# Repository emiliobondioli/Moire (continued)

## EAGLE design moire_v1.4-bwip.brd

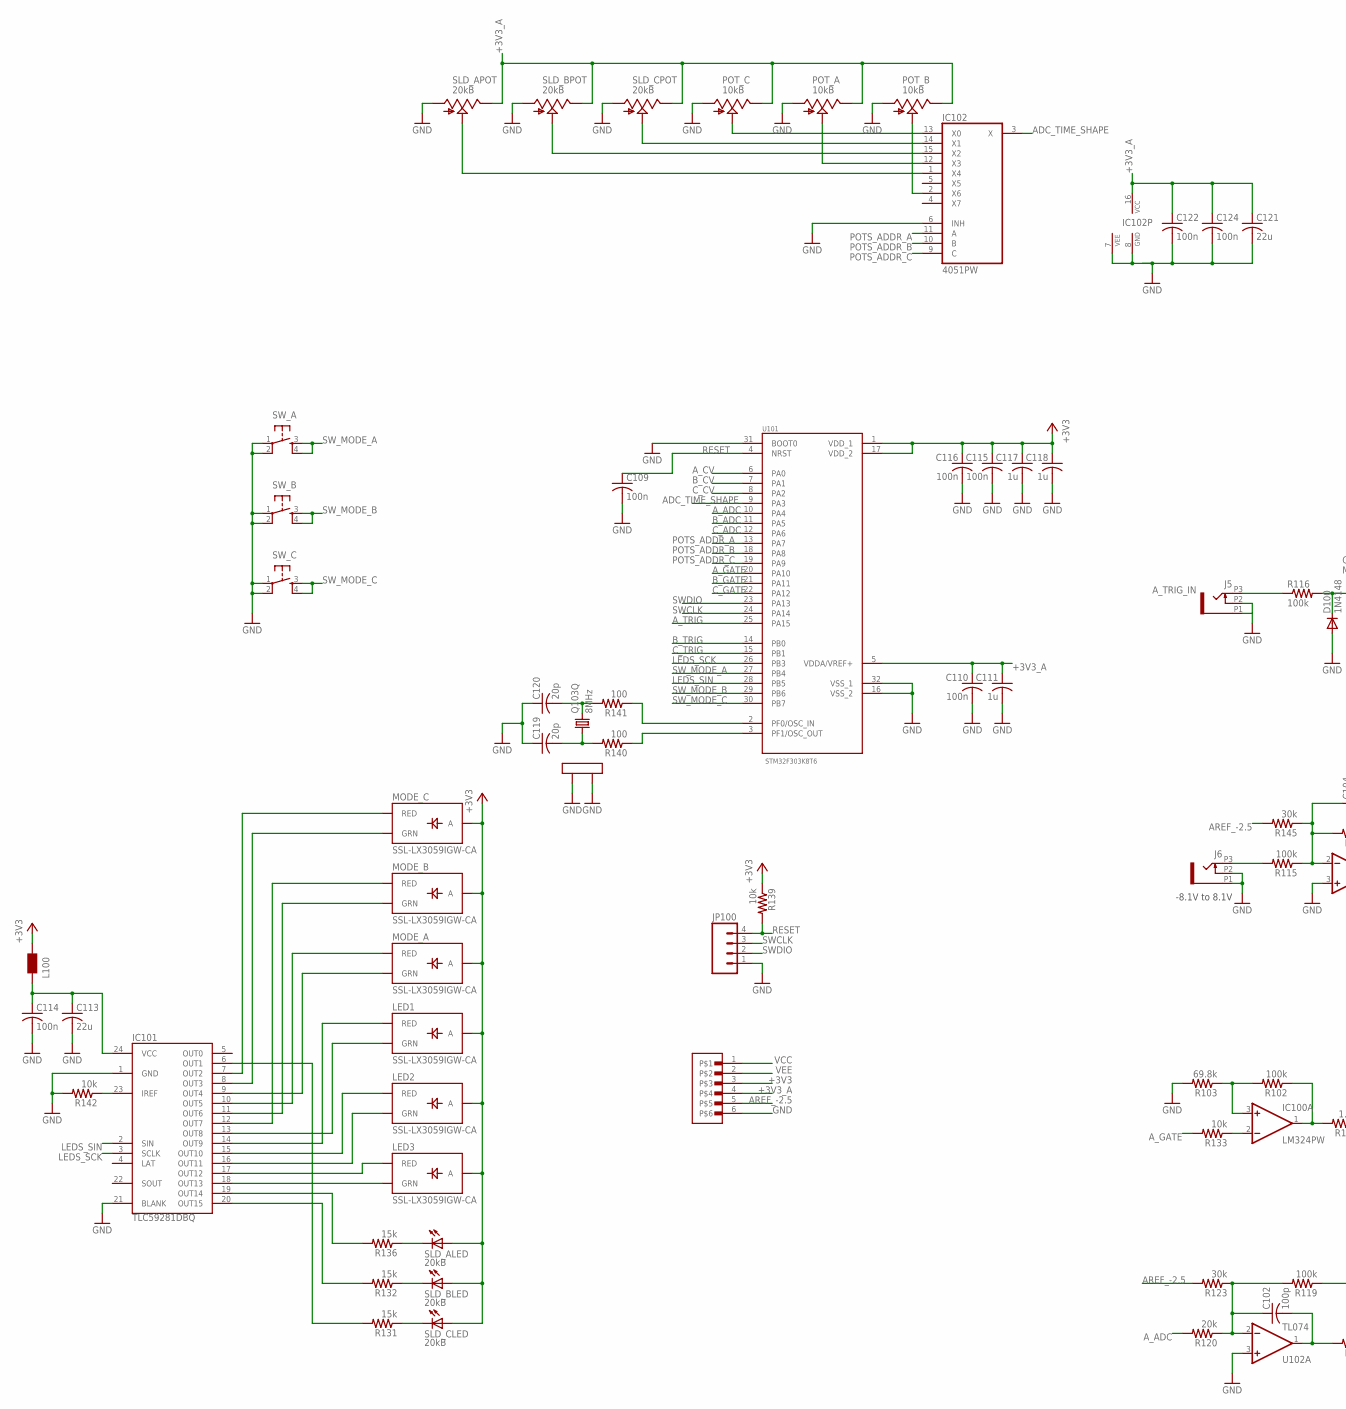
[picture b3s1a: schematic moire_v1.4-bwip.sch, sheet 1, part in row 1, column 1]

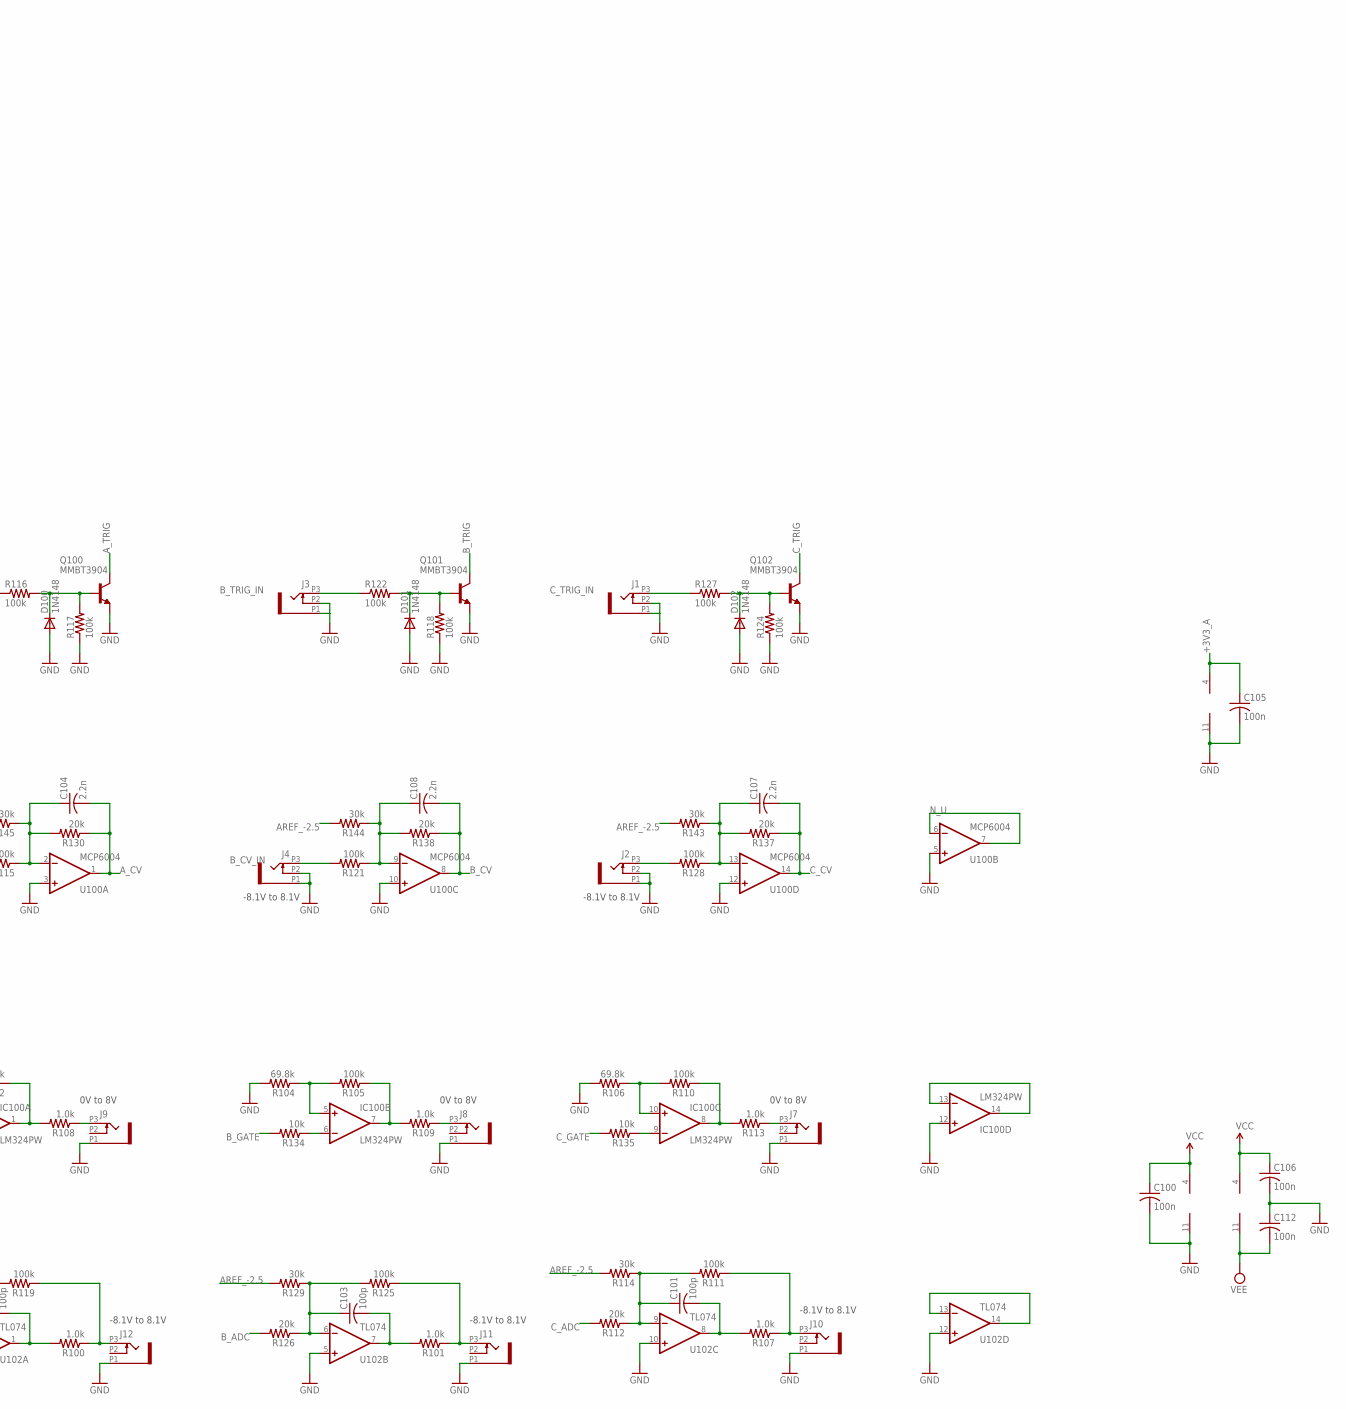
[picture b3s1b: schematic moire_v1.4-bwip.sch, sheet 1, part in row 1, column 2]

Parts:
C100, C105, C106, C109, C110, C112, C114, C115, C116, C122, C124: 100n; C0603
C101, C102, C103: 100p; C0603
C104, C107, C108: 2.2n; C0603
C111, C117, C118: 1u; C0603
C113, C121: 22u; C1206
C119, C120: 20p; C0603
D100, D101, D102: 1N4148; SOD523
IC100: LM324PW; TSSOP14_065
IC101: TLC59281DBQ; TSSOP24_0635
IC102: 4051PW; TSSOP16_065
J1, J2, J3, J4, J5, J6, J7, J8, J9, J10, J11, J12: PJ301_THONKICONN6; WQP_PJ_301M6
JP100: M04PTH; 1X04
L100: WE-CBF_0603; 0603
LED1, LED2, LED3: SSL-LX3059IGW-CA; LED-BICOLOR-THROUGHHOLE-LUMEX
MODE_A: SSL-LX3059IGW-CA; LED-BICOLOR-THROUGHHOLE-LUMEX
MODE_B: SSL-LX3059IGW-CA; LED-BICOLOR-THROUGHHOLE-LUMEX
MODE_C: SSL-LX3059IGW-CA; LED-BICOLOR-THROUGHHOLE-LUMEX
POT_A: 10kB; ALPS_POT_VERTICAL
POT_B: 10kB; ALPS_POT_VERTICAL
POT_C: 10kB; ALPS_POT_VERTICAL
Q100, Q101, Q102: MMBT3904; SOT23-BEC
Q103: 8MHz; CTS406
R100, R101, R107, R108, R109, R113: 1.0k; R0603
R102, R105, R110, R111, R115, R116, R117, R118, R119, R121, R122, R124, R125, R127, R128: 100k; R0603
R103, R104, R106: 69.8k; R0603
R112, R120, R126, R130, R137, R138: 20k; R0603
R114, R123, R129, R143, R144, R145: 30k; R0603
R131, R132, R136: 15k; R0603
R133, R134, R135, R139, R142: 10k; R0603
R140, R141: 100; R0603
SLD_A: 20kB; BOURNS_SLIDER
SLD_B: 20kB; BOURNS_SLIDER
SLD_C: 20kB; BOURNS_SLIDER
SW_A: TAC_SWITCHPTH; TACTILE-PTH
SW_B: TAC_SWITCHPTH; TACTILE-PTH
SW_C: TAC_SWITCHPTH; TACTILE-PTH
U100: MCP6004; SO14
U101: STM32F303K8T6; QFP80P900X900X160-32N
U102: TL074; SO14
U$1: 1X6-SMD-TESTPAD; 6X1-SMD-TESTPAD

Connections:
+3V3: C115.1, C116.1, C117.1, C118.1, L100.2, LED1.A, LED2.A, LED3.A, MODE_A.A, MODE_B.A, MODE_C.A, R139.1, SLD_A.B (A), SLD_B.B (A), SLD_C.B (A), U101.1 (VDD_1), U101.17 (VDD_2), U$1.3; also elsewhere on the board
+3V3_A: C105.1, C110.1, C111.1, C121.1, C122.1, C124.1, IC102.16 (VCC), POT_A.P$1 (E), POT_B.P$1 (E), POT_C.P$1 (E), SLD_A.3 (E), SLD_B.3 (E), SLD_C.3 (E), U100.4 (V+), U101.5 (VDDA/VREF+), U$1.4; also elsewhere on the board
ADC_TIME_SHAPE: IC102.3 (X), U101.9 (PA3)
AREF_-2.5: R114.2, R123.2, R129.2, R143.2, R144.2, R145.2, U$1.5; also elsewhere on the board
A_ADC: R120.2, U101.10 (PA4)
A_CV: C104.2, R130.1, U100.1 (OUT), U101.6 (PA0)
A_GATE: R133.2, U101.20 (PA10)
A_TRIG: Q100.C, U101.25 (PA15)
A_TRIG_IN: J5.P3 (3), R116.1
B_ADC: R126.2, U101.11 (PA5)
B_CV: C108.2, R138.1, U100.8 (OUT), U101.7 (PA1)
B_CV_IN: J4.P3 (3), R121.2
B_GATE: R134.2, U101.21 (PA11)
B_TRIG: Q101.C, U101.14 (PB0)
B_TRIG_IN: J3.P3 (3), R122.1
C_ADC: R112.2, U101.12 (PA6)
C_CV: C107.2, R137.1, U100.14 (OUT), U101.8 (PA2)
C_GATE: R135.2, U101.22 (PA12)
C_TRIG: Q102.C, U101.15 (PB1)
C_TRIG_IN: J1.P3 (3), R127.1
GND: C100.2, C105.2, C106.2, C109.2, C110.2, C111.2, C112.1, C113.2, C114.2, C115.2, C116.2, C117.2, C118.2, C119.1, C120.1, C121.2, C122.2, C124.2, D100.A, D101.A, D102.A, IC100.11 (V-), IC100.12 (+IN), IC101.1 (GND), IC101.21 (BLANK), IC102.6 (INH), IC102.7 (VEE), IC102.8 (GND), J1.P1 (1), J1.P2 (2), J2.P1 (1), J2.P2 (2), J3.P1 (1), J3.P2 (2), J4.P1 (1), J4.P2 (2), J5.P1 (1), J5.P2 (2), J6.P1 (1), J6.P2 (2), J7.P1 (1), J8.P1 (1), J9.P1 (1), J10.P1 (1), J11.P1 (1), J12.P1 (1), JP100.1, POT_A.P$3 (A), POT_B.P$3 (A), POT_C.P$3 (A), Q100.E, Q101.E, Q102.E, Q103.2 (LID1), Q103.4 (LID2), R103.2, R104.2, R106.2, R117.1, R118.1, R124.1, R142.2, SLD_A.1 (A), SLD_B.1 (A), SLD_C.1 (A), SW_A.1, SW_A.2, SW_B.1, SW_B.2, SW_C.1, SW_C.2, U100.3 (+IN), U100.5 (+IN), U100.10 (+IN), U100.11 (V-), U100.12 (+IN), U101.16 (VSS_2), U101.31 (BOOT0), U101.32 (VSS_1), U102.3 (+IN), U102.5 (+IN), U102.10 (+IN), U102.12 (+IN), U$1.6; also elsewhere on the board
LEDS_SCK: IC101.3 (SCLK), U101.26 (PB3)
LEDS_SIN: IC101.2 (SIN), U101.28 (PB5)
unnamed: R131.1, SLD_C.E (C)
unnamed: J9.P3 (3), R108.1
unnamed: IC100.13 (-IN), IC100.14 (OUT)
unnamed: J11.P3 (3), R101.1, R125.1
unnamed: C103.1, R125.2, R126.1, R129.1, U102.6 (-IN)
unnamed: R141.1, U101.2 (PF0/OSC_IN)
unnamed: R140.1, U101.3 (PF1/OSC_OUT)
unnamed: C120.2, Q103.3 (2), R141.2
unnamed: C119.2, Q103.1, R140.2
unnamed: J8.P3 (3), R109.1
unnamed: U102.13 (-IN), U102.14 (OUT)
unnamed: C103.2, R101.2, U102.7 (OUT)
unnamed: IC100.1 (OUT), R102.1, R108.2
unnamed: J10.P3 (3), R107.1, R111.1
unnamed: C101.1, R111.2, R112.1, R114.1, U102.9 (-IN)
unnamed: C101.2, R107.2, U102.8 (OUT)
unnamed: J7.P3 (3), R113.1
unnamed: J2.P3 (3), R128.2
unnamed: J6.P3 (3), R115.2
unnamed: IC100.3 (+IN), R102.2, R103.1
unnamed: IC100.2 (-IN), R133.1
unnamed: IC100.7 (OUT), R105.1, R109.2
unnamed: IC100.5 (+IN), R104.1, R105.2
unnamed: IC100.6 (-IN), R134.1
unnamed: IC100.8 (OUT), R110.1, R113.2
unnamed: IC101.11 (OUT6), MODE_B.GREEN_C (GRN)
unnamed: IC101.10 (OUT5), MODE_A.RED_C (RED)
unnamed: IC101.12 (OUT7), MODE_B.RED_C (RED)
unnamed: IC101.7 (OUT2), MODE_C.RED_C (RED)
unnamed: IC101.8 (OUT3), MODE_C.GREEN_C (GRN)
unnamed: IC101.15 (OUT10), LED2.RED_C (RED)
unnamed: IC101.16 (OUT11), LED2.GREEN_C (GRN)
unnamed: IC101.13 (OUT8), LED1.GREEN_C (GRN)
unnamed: IC101.17 (OUT12), LED3.RED_C (RED)
unnamed: D102.C, Q102.B, R124.2, R127.2
unnamed: IC101.18 (OUT13), LED3.GREEN_C (GRN)
unnamed: IC101.14 (OUT9), LED1.RED_C (RED)
unnamed: C113.1, C114.1, IC101.24 (VCC), L100.1
unnamed: IC101.19 (OUT14), R136.2
unnamed: IC101.20 (OUT15), R132.2
unnamed: IC101.6 (OUT1), R131.2
unnamed: IC102.1 (X4), SLD_A.2 (S)
unnamed: R132.1, SLD_B.E (C)
unnamed: R136.1, SLD_A.E (C)
unnamed: IC102.2 (X6), POT_B.P$2 (S)
unnamed: IC102.12 (X3), POT_A.P$2 (S)
unnamed: IC102.13 (X0), POT_C.P$2 (S)
unnamed: IC102.14 (X1), SLD_C.2 (S)
unnamed: IC102.15 (X2), SLD_B.2 (S)
unnamed: C104.1, R115.1, R130.2, R145.1, U100.2 (-IN)
unnamed: C108.1, R121.1, R138.2, R144.1, U100.9 (-IN)
unnamed: C107.1, R128.1, R137.2, R143.1, U100.13 (-IN)
unnamed: IC100.10 (+IN), R106.1, R110.2
unnamed: D101.C, Q101.B, R118.2, R122.2
unnamed: IC100.9 (-IN), R135.1
unnamed: D100.C, Q100.B, R116.2, R117.2
unnamed: IC101.23 (IREF), R142.1
unnamed: J12.P3 (3), R100.1, R119.1
unnamed: C102.1, R119.2, R120.1, R123.1, U102.2 (-IN)
unnamed: C102.2, R100.2, U102.1 (OUT)
unnamed: IC101.9 (OUT4), MODE_A.GREEN_C (GRN)
N_U: U100.6 (-IN), U100.7 (OUT)
POTS_ADDR_A: IC102.11 (A), U101.13 (PA7)
POTS_ADDR_B: IC102.10 (B), U101.18 (PA8)
POTS_ADDR_C: IC102.9 (C), U101.19 (PA9)
RESET: C109.1, JP100.4, R139.2, U101.4 (NRST)
SWCLK: JP100.3, U101.24 (PA14)
SWDIO: JP100.2, U101.23 (PA13)
SW_MODE_A: SW_A.3, SW_A.4, U101.27 (PB4)
SW_MODE_B: SW_B.3, SW_B.4, U101.29 (PB6)
SW_MODE_C: SW_C.3, SW_C.4, U101.30 (PB7)
VCC: C100.1, C106.1, IC100.4 (V+), U102.4 (V+), U$1.1; also elsewhere on the board
VEE: C112.2, U102.11 (V-), U$1.2; also elsewhere on the board

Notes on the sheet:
-8.1V to 8.1V
0V to 8V

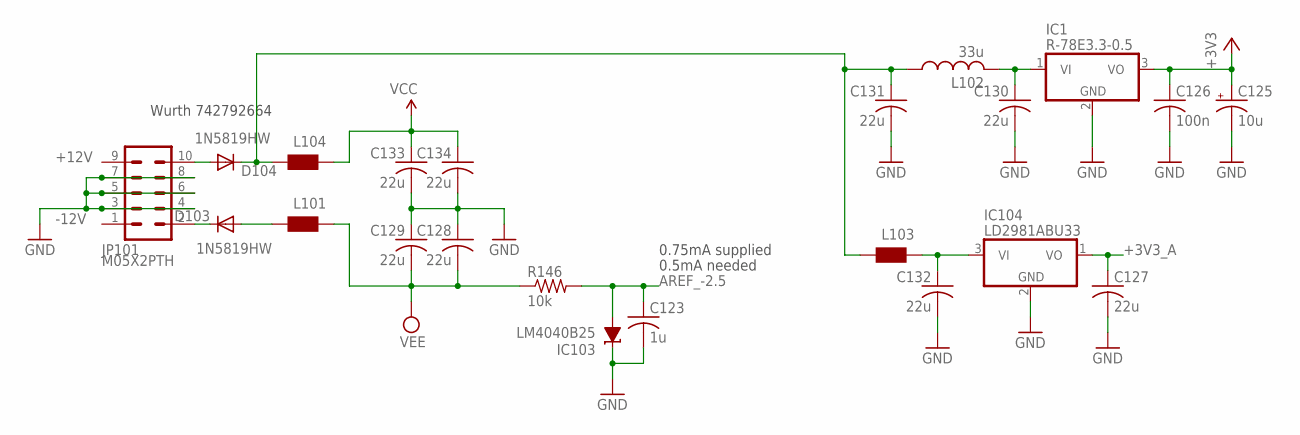
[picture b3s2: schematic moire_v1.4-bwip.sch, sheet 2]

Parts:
C123: 1u; C0603
C125: 10u; PANASONIC_A
C126: 100n; C0603
C127, C128, C129, C130, C131, C132, C133, C134: 22u; C1206
D103, D104: 1N5819HW; SOD123
IC1: R-78E3.3-0.5; WE78
IC103: LM4040B25; DBZ_R-PDSO-G3
IC104: LD2981ABU33; SOT89
JP101: M05X2PTH; 2X5-PTH
L101, L103, L104: WE-CBF_0603; 0603
L102: 33u; L2012C
R146: 10k; R0603

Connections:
+3V3: C125.+, C126.1, IC1.3 (VO); also elsewhere on the board
+3V3_A: C127.1, IC104.1 (VO); also elsewhere on the board
+12V: D104.A, JP101.9, JP101.10
-12V: D103.C, JP101.1, JP101.2
AREF_-2.5: C123.1, IC103.2 (A), R146.2; also elsewhere on the board
GND: C123.2, C125.-, C126.2, C127.2, C128.1, C129.1, C130.2, C131.2, C132.2, C133.2, C134.2, IC1.2 (GND), IC103.1 (C), IC104.2 (GND), JP101.3, JP101.4, JP101.5, JP101.6, JP101.7, JP101.8; also elsewhere on the board
unnamed: D103.A, L101.2
unnamed: C131.1, D104.C, L102.1, L103.2, L104.2
unnamed: C132.1, IC104.3 (VI), L103.1
unnamed: C130.1, IC1.1 (VI), L102.2
VCC: C133.1, C134.1, L104.1; also elsewhere on the board
VEE: C128.2, C129.2, L101.1, R146.1; also elsewhere on the board

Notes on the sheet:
0.5mA needed
Wurth 742792664
0.75mA supplied

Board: 2 copper layers, 135 parts (107 on the bottom side), 102 nets, no tracks yet.
